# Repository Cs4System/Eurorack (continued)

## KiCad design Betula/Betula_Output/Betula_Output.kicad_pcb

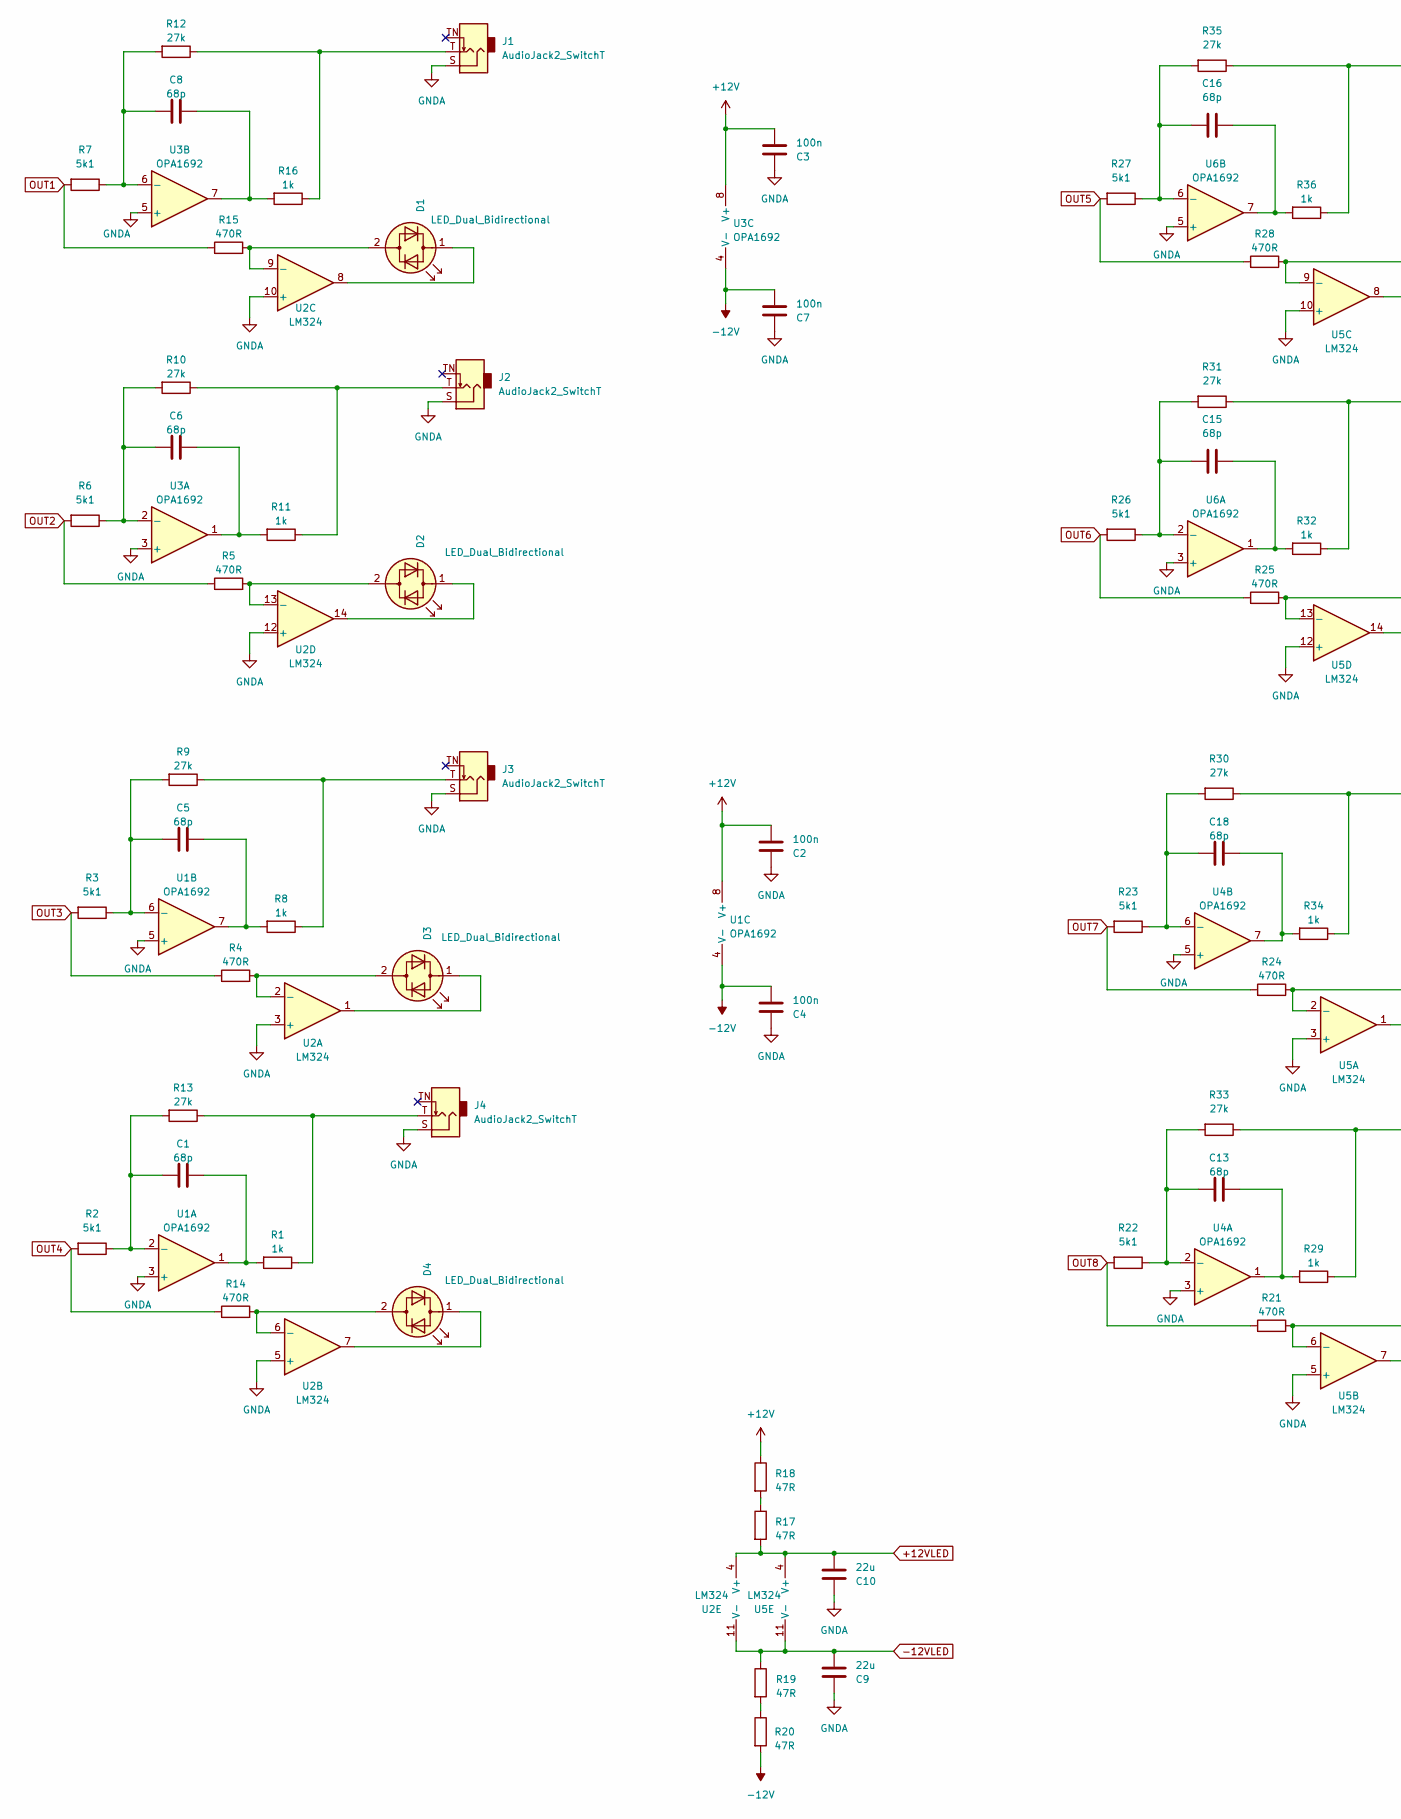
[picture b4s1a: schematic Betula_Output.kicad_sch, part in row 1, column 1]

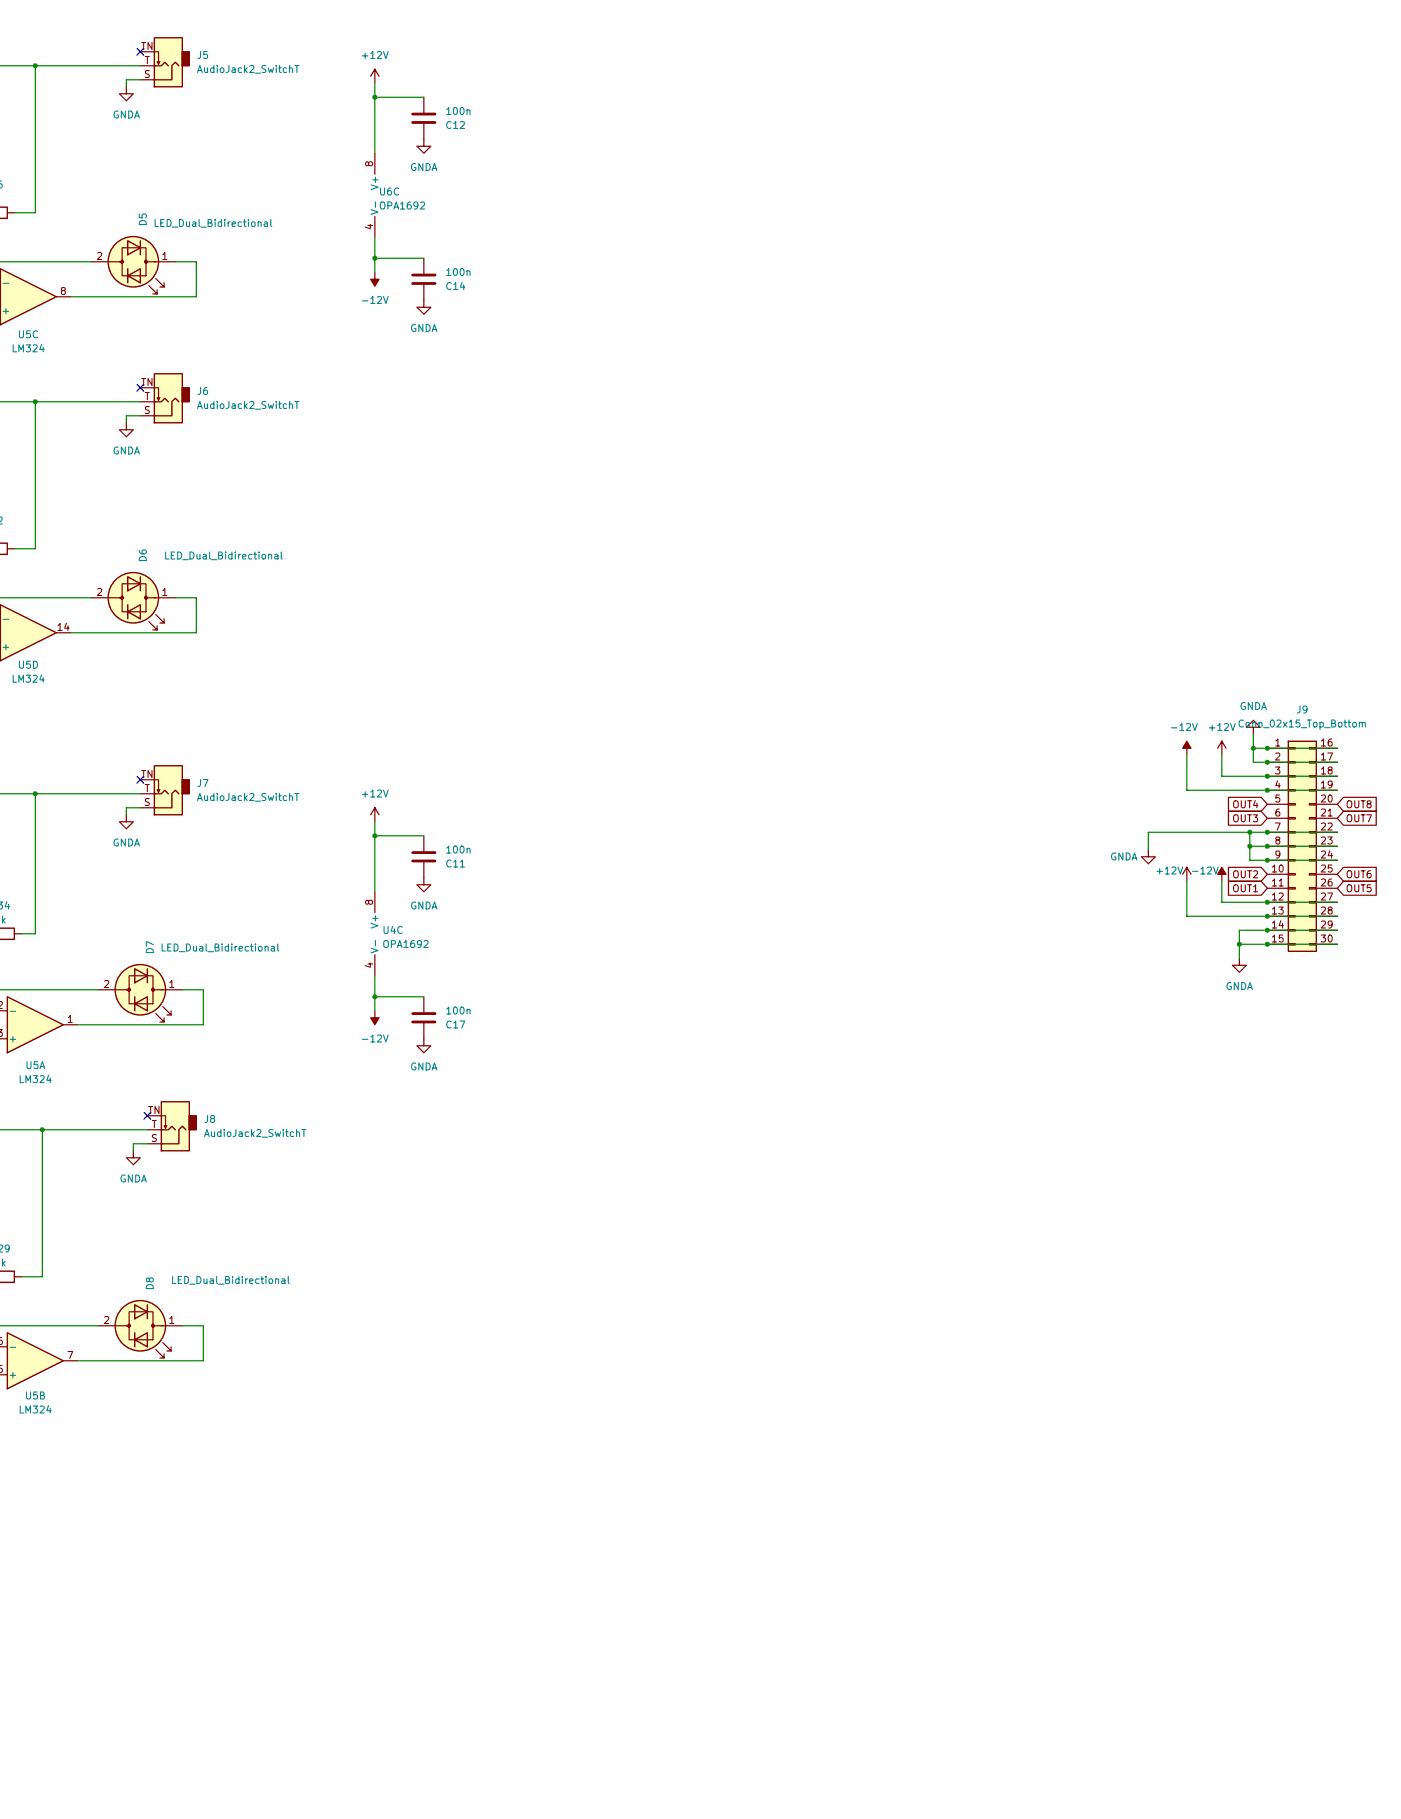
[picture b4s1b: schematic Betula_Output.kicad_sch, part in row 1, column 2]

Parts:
C1, C5, C6, C8, C13, C15, C16, C18: 68p; C_0603_1608Metric_Pad1.08x0.95mm_HandSolder
C2, C3, C4, C7, C11, C12, C14, C17: 100n; C_0603_1608Metric_Pad1.08x0.95mm_HandSolder
C9, C10: 22u; C_0805_2012Metric_Pad1.18x1.45mm_HandSolder
D1, D2, D3, D4, D5, D6, D7, D8: LED_Dual_Bidirectional; LED_D3.0mm
J1, J2, J3, J4, J5, J6, J7, J8: AudioJack2_SwitchT; Thonkicon
J9: Conn_02x15_Top_Bottom; Output-Main
R1, R8, R11, R16, R29, R32, R34, R36: 1k; R_0603_1608Metric_Pad0.98x0.95mm_HandSolder
R2, R3, R6, R7, R22, R23, R26, R27: 5k1; R_0603_1608Metric_Pad0.98x0.95mm_HandSolder
R4, R5, R14, R15, R21, R24, R25, R28: 470R; R_0603_1608Metric_Pad0.98x0.95mm_HandSolder
R9, R10, R12, R13, R30, R31, R33, R35: 27k; R_0603_1608Metric_Pad0.98x0.95mm_HandSolder
R17, R18, R19, R20: 47R; R_0603_1608Metric_Pad0.98x0.95mm_HandSolder
U1, U3, U4, U6: OPA1692; SOIC-8_3.9x4.9mm_P1.27mm
U2, U5: LM324; SOIC-14_3.9x8.7mm_P1.27mm

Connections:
+12V: C2.2, C3.2, C11.2, C12.2, J9.3, J9.13, J9.18, J9.28, R18.1, U1.8 (V+), U3.8 (V+), U4.8 (V+), U6.8 (V+)
+12VLED: C10.2, R17.2, U2.4 (V+), U5.4 (V+)
-12V: C4.2, C7.2, C14.2, C17.2, J9.4, J9.12, J9.19, J9.27, R20.2, U1.4 (V-), U3.4 (V-), U4.4 (V-), U6.4 (V-)
-12VLED: C9.2, R19.1, U2.11 (V-), U5.11 (V-)
GNDA: C2.1, C3.1, C4.1, C7.1, C9.1, C10.1, C11.1, C12.1, C14.1, C17.1, J1.S, J2.S, J3.S, J4.S, J5.S, J6.S, J7.S, J8.S, J9.1, J9.2, J9.7, J9.8, J9.9, J9.14, J9.15, J9.16, J9.17, J9.22, J9.23, J9.24, J9.29, J9.30, U1.3 (+), U1.5 (+), U2.3 (+), U2.5 (+), U2.10 (+), U2.12 (+), U3.3 (+), U3.5 (+), U4.3 (+), U4.5 (+), U5.3 (+), U5.5 (+), U5.10 (+), U5.12 (+), U6.3 (+), U6.5 (+)
unnamed: C1.2, R1.2, U1.1
unnamed: C5.2, R8.2, U1.7
unnamed: C6.2, R11.2, U3.1
unnamed: C8.2, R16.2, U3.7
unnamed: C13.2, R29.2, U4.1
unnamed: C15.1, R32.2, U6.1
unnamed: C18.2, R34.2, U4.7
unnamed: C16.2, R36.2, U6.7
unnamed: D1.2 (AK), R15.2, U2.9 (-)
unnamed: D1.1 (KA), U2.8
unnamed: D2.2 (AK), R5.2, U2.13 (-)
unnamed: D2.1 (KA), U2.14
unnamed: D3.2 (AK), R4.2, U2.2 (-)
unnamed: D3.1 (KA), U2.1
unnamed: D4.2 (AK), R14.2, U2.6 (-)
unnamed: D4.1 (KA), U2.7
unnamed: D5.2 (AK), R28.1, U5.9 (-)
unnamed: D5.1 (KA), U5.8
unnamed: D6.2 (AK), R25.2, U5.13 (-)
unnamed: D6.1 (KA), U5.14
unnamed: D7.2 (AK), R24.1, U5.2 (-)
unnamed: D7.1 (KA), U5.1
unnamed: D8.2 (AK), R21.2, U5.6 (-)
unnamed: D8.1 (KA), U5.7
unnamed: J1.T, R12.1, R16.1
unnamed: J2.T, R10.1, R11.1
unnamed: J3.T, R8.1, R9.1
unnamed: J4.T, R1.1, R13.1
unnamed: J5.T, R35.1, R36.1
unnamed: J6.T, R31.1, R32.1
unnamed: J7.T, R30.1, R34.1
unnamed: J8.T, R29.1, R33.1
unnamed: R17.1, R18.2
unnamed: R19.2, R20.1
unnamed: C1.1, R2.1, R13.2, U1.2 (-)
unnamed: C5.1, R3.1, R9.2, U1.6 (-)
unnamed: C6.1, R6.1, R10.2, U3.2 (-)
unnamed: C8.1, R7.1, R12.2, U3.6 (-)
unnamed: C13.1, R22.1, R33.2, U4.2 (-)
unnamed: C18.1, R23.1, R30.2, U4.6 (-)
unnamed: C15.2, R26.1, R31.2, U6.2 (-)
unnamed: C16.1, R27.1, R35.2, U6.6 (-)
OUT1: J9.11, R7.2, R15.1
OUT2: J9.10, R5.1, R6.2
OUT3: J9.6, R3.2, R4.1
OUT4: J9.5, R2.2, R14.1
OUT5: J9.26, R27.2, R28.2
OUT6: J9.25, R25.1, R26.2
OUT7: J9.21, R23.2, R24.2
OUT8: J9.20, R21.1, R22.2

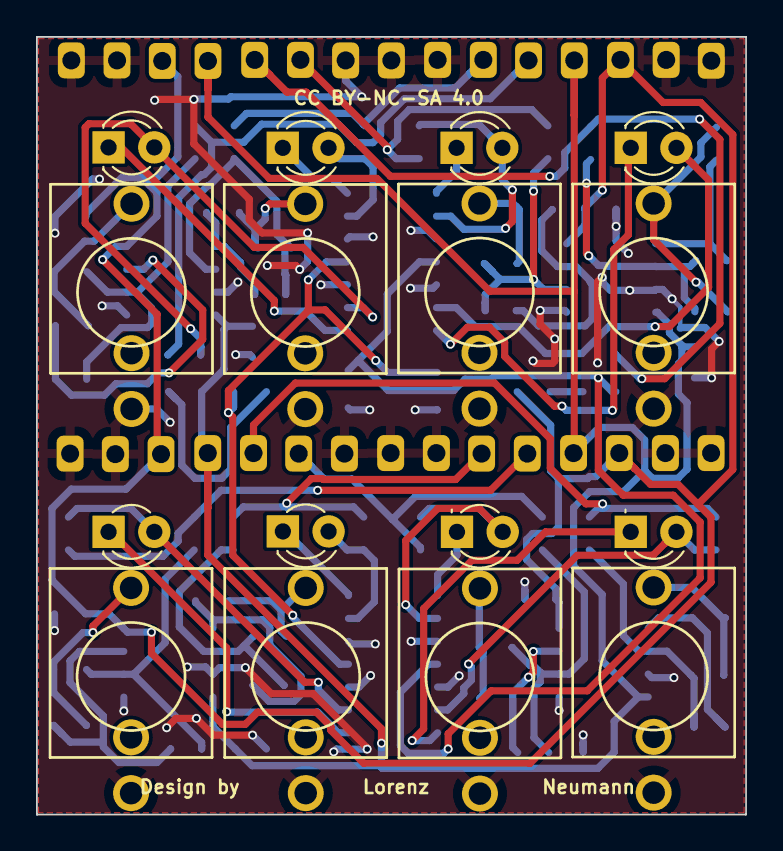
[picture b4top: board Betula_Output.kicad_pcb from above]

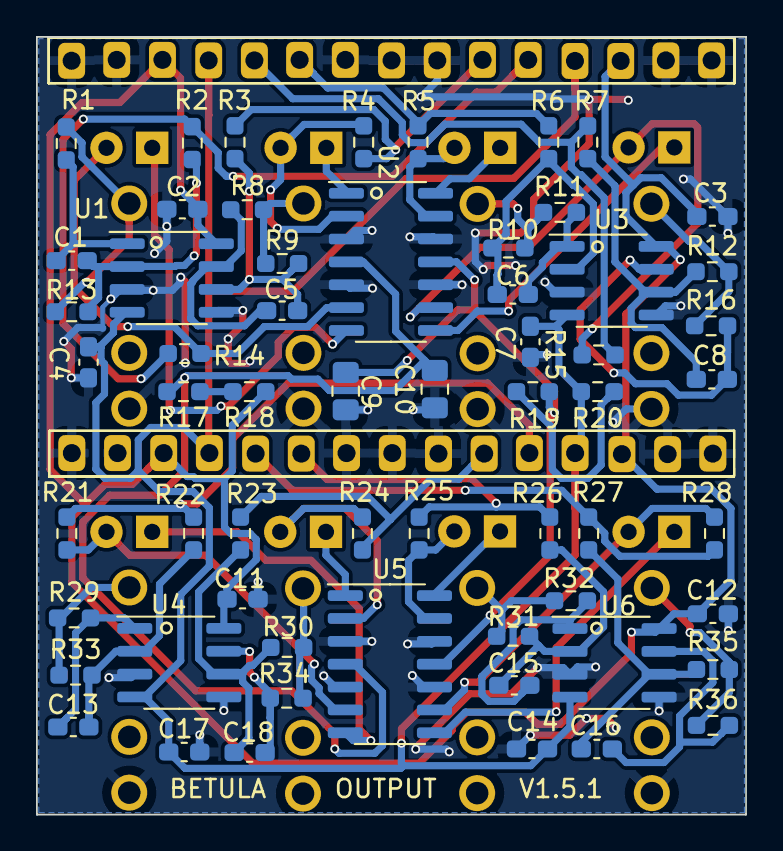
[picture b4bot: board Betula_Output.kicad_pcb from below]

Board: 2 copper layers, 39.4 x 43.2 mm, 77 parts (60 on the bottom side), 55 nets.

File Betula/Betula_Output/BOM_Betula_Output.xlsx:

Reference(s) | Qty | Value | Footprint | Mouser | Comment
R9,R10,R12,R13,R30,R31,R33,R35 | 8 | 27k | R_0603 | 603-RC0603FR-0727KL
R2, R3, R6, R7, R22, R23, R26, R27 | 8 | 5k1 | R_0603 | 603-RC0603FR-075K1L
R1, R8, R11, R16, R29, R32, R34, R36 | 8 | 1k | R_0603 | 603-RC0603FR-071KL
R4, R5, R14, R15, R21, R24, R25, R28 | 8 | 470R | R_0603 | 603-RC0603FR-07470RL
R17,R18,R19,R20 | 4 | 47R | R_0603 | 603-RC0603FR-0747RL
C1, C5, C6, C8, C13, C15, C16, C18 | 8 | 68p | C_0603 | 187-CL10C680JB8NNNC | C0G Type!
C2, C3, C4, C7, C11, C12, C14, C17 | 8 | 100n | C_0603 | 80-C0603C104J5RACLR
C9,C10 | 2 | 22u | C_0805 | 187-CL21A226MAYNNNE
U1, U3, U4, U6 | 4 | OPA1692 | SOIC-8_3.9x4.9mm_P1.27mm | 595-OPA1692IDR | TL072C works as well. Higher currend draw ( + 6mA on both rails)
U2,U5 | 2 | LM324 | SOIC-14_3.9x8.7mm_P1.27mm | 595-LM324DR
D1, D2, D3, D4, D5, D6, D7, D8 | 8 | LED_Dual_Bidirectional | LED_D3.0mm | 604-WP937EGW
J1, J2, J3, J4, J5, J6, J7, J8 | 8 | Thonkicon
J9 | 2 | 15x1 Pin Header |  | 855-M20-9991546

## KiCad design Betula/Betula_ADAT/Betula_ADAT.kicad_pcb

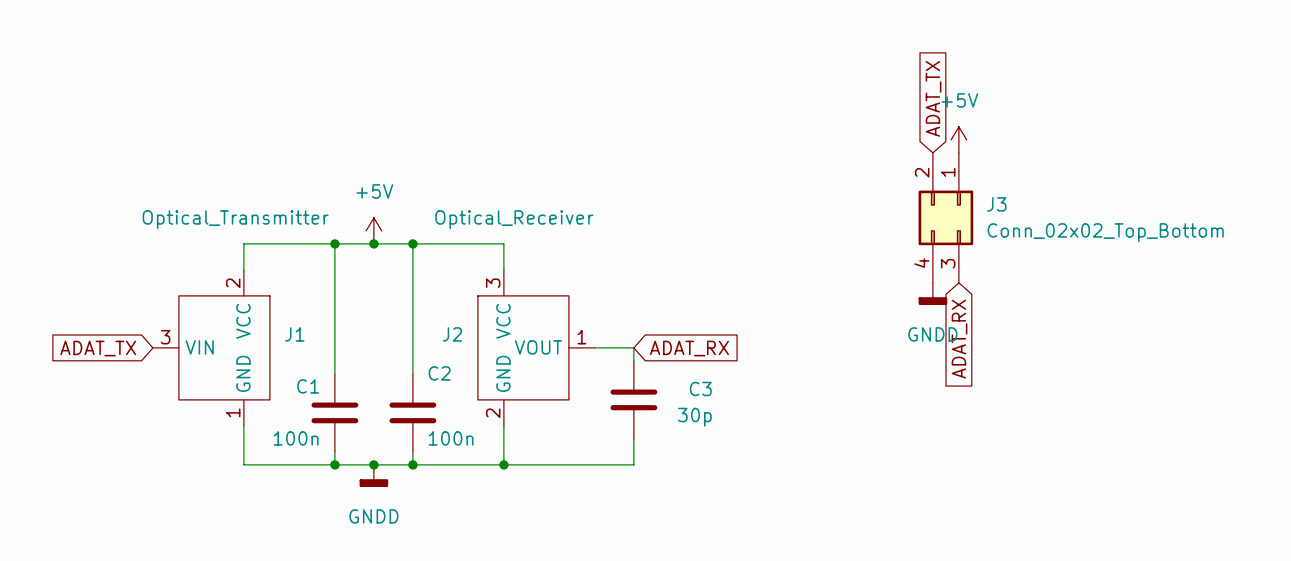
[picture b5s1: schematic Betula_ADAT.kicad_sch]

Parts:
C1, C2: 100n; C_0603_1608Metric_Pad1.08x0.95mm_HandSolder
C3: 30p; C_0603_1608Metric_Pad1.08x0.95mm_HandSolder
J1: Optical_Transmitter; Optical_Jack
J2: Optical_Receiver; Optical_Jack
J3: Conn_02x02_Top_Bottom; PinHeader_2x02_P2.54mm_Horizontal

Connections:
+5V: C1.2, C2.2, J1.2 (VCC), J2.3 (VCC), J3.1
ADAT_RX: C3.2, J2.1 (VOUT), J3.3
ADAT_TX: J1.3 (VIN), J3.2
GNDD: C1.1, C2.1, C3.1, J1.1 (GND), J2.2 (GND), J3.4

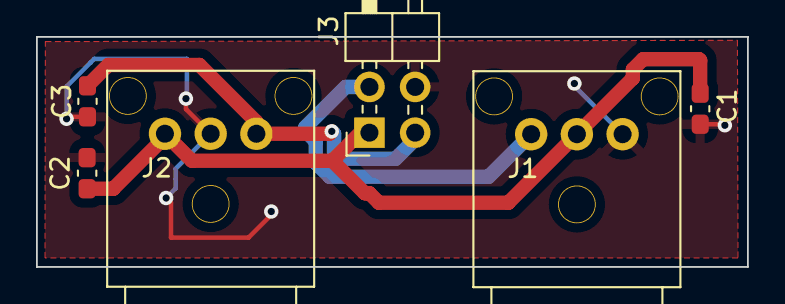
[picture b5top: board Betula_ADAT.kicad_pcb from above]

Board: 2 copper layers, 39.5 x 12.8 mm, 6 parts (0 on the bottom side), 4 nets.

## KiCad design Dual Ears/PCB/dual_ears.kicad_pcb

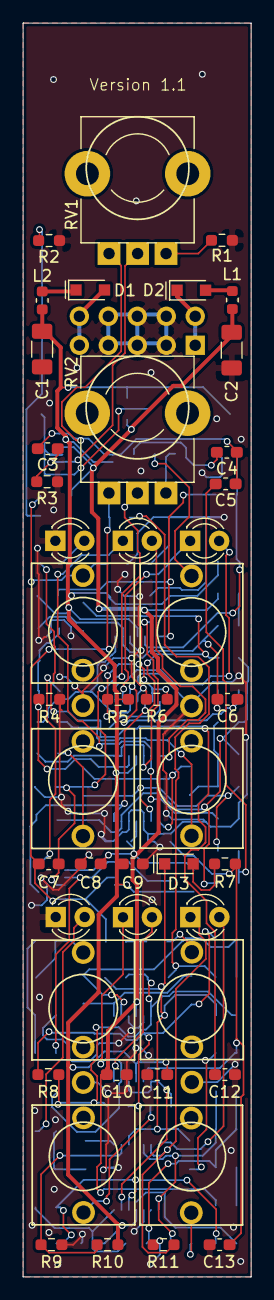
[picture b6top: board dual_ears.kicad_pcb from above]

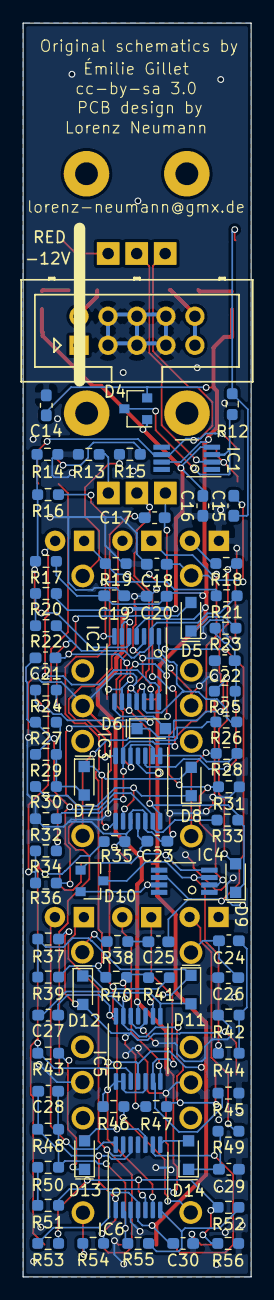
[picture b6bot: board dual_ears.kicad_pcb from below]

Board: 2 copper layers, 20.0 x 110.0 mm, 125 parts (80 on the bottom side), 73 nets.

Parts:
C1, C2: 22u; C_1206_3216Metric_Pad1.33x1.80mm_HandSolder
C3, C7: 22p; C_0603_1608Metric_Pad1.05x0.95mm_HandSolder
C4, C5, C15, C17, C24, C25: 4.7u; C_0603_1608Metric_Pad1.05x0.95mm_HandSolder
C6, C18, C26, C28: 68p; C_0603_1608Metric_Pad1.05x0.95mm_HandSolder
C8, C9, C10, C11, C14, C16, C19, C20, C23, C30: 100n; C_0603_1608Metric_Pad1.05x0.95mm_HandSolder
C12, C13, C22, C29: 1u; C_0603_1608Metric_Pad1.05x0.95mm_HandSolder
C21, C27: 1.0n; C_0603_1608Metric_Pad1.05x0.95mm_HandSolder
D1, D2: PMEG2010AEB; D_SOD-323_HandSoldering
D3, D5, D6, D7, D8, D9, D11, D12, D13, D14: 1N4148; D_SOD-323_HandSoldering
D4, D10: DNP; D_SOT-23
IC1, IC4: OPA1641; VSSOP-8_3.0x3.0mm_P0.65mm
IC2, IC3, IC5, IC6: LM324PW; TSSOP-14_4.4x5mm_P0.65mm
J1, J2, J5, J6: Audio-Jack-2_Switch; Thonkicon
J3, J4, J7, J8: Audio-Jack-2_Switch; Thonkicon_noGND
JP1: M05X2PTH; Multicomp_MC9A12-1034_2x05x2.54mm_Straight
L1, L2: WE-CBF_0603; L_0603_1608Metric
LED1, LED4: WP710A10SEC/J3; LED_D3.0mm
LED2, LED6: AOL-3MWY4; LED_D3.0mm
LED3, LED5: WP710A10SEC/J4; LED_D3.0mm
R1, R13, R15, R26, R28, R38, R46, R54: 510; R_0603_1608Metric_Pad0.98x0.95mm_HandSolder
R2, R4, R35, R42: 1.0M; R_0603_1608Metric_Pad0.98x0.95mm_HandSolder
R3, R7, R11, R12, R18, R19, R25, R31, R44, R49: 10k; R_0603_1608Metric_Pad0.98x0.95mm_HandSolder
R5, R10, R32, R45: 20k; R_0603_1608Metric_Pad0.98x0.95mm_HandSolder
R6, R8, R9, R20, R27, R29, R30, R37, R47, R51: 100k; R_0603_1608Metric_Pad0.98x0.95mm_HandSolder
R14, R56: 15k; R_0603_1608Metric_Pad0.98x0.95mm_HandSolder
R16, R17, R21, R22, R24, R33, R34, R36, R39, R40, R41, R48, R50, R52, R53, R55: 200k; R_0603_1608Metric_Pad0.98x0.95mm_HandSolder
R23, R43: 2k7; R_0603_1608Metric_Pad0.98x0.95mm_HandSolder
RV1, RV2: 50kB; Potentiometer_Alps_RK09K_Horizontal

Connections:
/ears_v40_2/CLIP_1: D6.2, IC2.8
/ears_v40_2/CLIP_2: D14.2, IC6.8
/ears_v40_2/ENVELOPE_1: IC2.6, IC3.1, IC3.2, IC3.5, R28.1
/ears_v40_2/ENVELOPE_2: IC5.1, IC5.2, IC5.5, IC6.6, R46.1
/ears_v40_2/FULL_WAVE_RECT_1: C21.2, D5.2, D9.1, IC2.10, IC3.14, R33.2
/ears_v40_2/FULL_WAVE_RECT_2: C27.2, D3.1, D13.2, IC5.14, IC6.10, R41.2
/ears_v40_2/GATE_1: C6.2, IC2.1, IC2.12, R24.2, R26.1
/ears_v40_2/GATE_2: C28.2, IC6.1, IC6.12, R48.2, R54.1
/ears_v40_2/~GATE_1: IC2.7, R16.2, R21.1
/ears_v40_2/~GATE_2: IC6.7, R52.2, R55.1
AMP_OUT_1: C3.2, C4.1, C5.1, IC1.6, RV1.3
AMP_OUT_2: C7.2, C17.1, C25.1, IC4.6, RV2.3
GND: C1.2, C2.1, C8.1, C9.2, C10.1, C11.2, C12.2, C13.2, C14.2, C16.1, C18.2, C19.2, C20.2, C22.2, C23.1, C26.2, C29.2, C30.2, IC2.3, IC2.11, IC3.10, IC3.12, IC5.10, IC5.12, IC6.3, IC6.11, J1.2, J2.2, J5.2, J6.2, JP1.3, JP1.4, JP1.5, JP1.6, JP1.7, JP1.8, LED1.1, LED4.1, R1.2, R2.1, R3.2, R4.1, R6.1, R9.1, R11.1, R13.2, R14.2, R19.1, R31.2, R32.2, R35.1, R42.1, R45.2, R56.2
unnamed: C3.1, IC1.2, R3.1, RV1.2
unnamed: C4.2, R15.1
unnamed: C5.2, R34.1, R36.1
unnamed: C6.1, IC2.2, R21.2, R22.2, R24.1
unnamed: C7.1, IC4.2, R31.1, RV2.2
unnamed: C12.1, D6.1, R18.2
unnamed: C13.1, IC5.3, R7.2, R35.2, R43.2
unnamed: C15.1, C18.1, J1.1
unnamed: C15.2, R2.2, R12.2
unnamed: C17.2, R39.1, R40.1
unnamed: C21.1, IC3.13, R27.2, R29.2, R33.1, R36.2
unnamed: C22.1, IC3.3, R4.2, R23.2, R25.2
unnamed: C24.1, C26.1, J6.1
unnamed: C24.2, R42.2, R44.2
unnamed: C25.2, R38.1
unnamed: C27.1, IC5.13, R8.2, R40.2, R41.1, R47.2
unnamed: C28.1, IC6.2, R48.1, R50.2, R55.2
unnamed: C29.1, D14.1, R49.2
unnamed: D1.1, L2.2
unnamed: D1.2, JP1.9, JP1.10
unnamed: D2.1, JP1.1, JP1.2
unnamed: D2.2, L1.2
unnamed: D3.2, R7.1
unnamed: D4.3, IC1.3, R12.1
unnamed: D5.1, R23.1
unnamed: D7.1, D8.2, IC3.8
unnamed: D7.2, R27.1, R29.1, R30.2
unnamed: D8.1, IC3.9, R30.1, R34.2
unnamed: D9.2, R25.1
unnamed: D10.3, IC4.3, R44.1
unnamed: D11.1, IC5.9, R37.1, R39.2
unnamed: D11.2, D12.1, IC5.8
unnamed: D12.2, R8.1, R37.2, R47.1
unnamed: D13.1, R43.1
unnamed: IC2.5, R14.1, R16.1, R17.2
unnamed: IC2.9, R5.1, R6.2
unnamed: IC2.13, LED3.1, R19.2
unnamed: IC2.14, LED3.2
unnamed: IC3.6, LED2.1, R32.1
unnamed: IC3.7, LED2.2
unnamed: IC5.6, LED6.1, R45.1
unnamed: IC5.7, LED6.2
unnamed: IC6.5, R52.1, R53.2, R56.1
unnamed: IC6.9, R9.2, R10.1
unnamed: IC6.13, LED5.1, R11.2
unnamed: IC6.14, LED5.2
unnamed: J2.1, R15.2
unnamed: J3.1, R26.2
unnamed: J4.1, R28.2
unnamed: J5.1, R38.2
unnamed: J7.1, R46.2
unnamed: J8.1, R54.2
unnamed: LED1.2, R18.1
unnamed: LED4.2, R49.1
unnamed: R1.1, RV1.1
unnamed: R13.1, RV2.1
unnamed: R20.1, R22.1
unnamed: R50.1, R51.1
VCC: C1.1, C9.1, C11.1, C14.1, C19.1, C20.1, C30.1, D4.2, D10.2, IC1.7, IC2.4, IC3.4, IC4.7, IC5.4, IC6.4, L2.1, R5.2, R10.2, R17.1, R53.1
VEE: C2.2, C8.2, C10.2, C16.2, C23.2, D4.1, D10.1, IC1.4, IC3.11, IC4.4, IC5.11, L1.1, R20.2, R51.2

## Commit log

2021-02-06 Update PCB files
2021-02-08 Updated some resistor values
2021-02-09 smaler fixes
2021-02-09 added PCB pictures
2021-02-10 Minor changes PCB
2021-02-11 Updated BOM
2021-02-11 Updated schematics
2021-02-14 Updated picture
2021-02-24 Updated schematics and BOM
2021-03-07 improved documentation
2021-06-07 update documentation
2024-06-28 Betula: removed loose label
2024-06-28 Betula: Updated some part labels in schematics
2024-06-28 Initial commit for Betula with v1.4.2
2024-06-28 Added Betula v1.5.1: Improved noise floor, 4-layer main PCB, better Panel
2024-06-28 Incremented all version numbers to 1.5.1 on all PCBs
2024-06-28 fixed 2mm via to 3mm in order to avoid extra cost in manufacturing
2024-07-16 Panel: Added more clearance between silkscreen and soldermask
2024-07-20 Updated documentation
2024-08-07 Formated BOM for main PCB
2024-11-03 Changed DC/DC converters to R-78Kx, updated to v1.5.2
2025-01-25 Fixed small via, that would course extra cost in production
2025-01-29 Added gitignore
2025-01-29 Salix (Transistor Ladder VCF v1.3) Initial commit
2025-01-29 Salix Updated Documentation
2025-02-19 Added BOM for pre-assembled PCBs
2025-02-23 Small fix in Input PCB BOM
